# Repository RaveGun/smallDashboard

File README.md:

smallDashboard
==============

Small Dashboard

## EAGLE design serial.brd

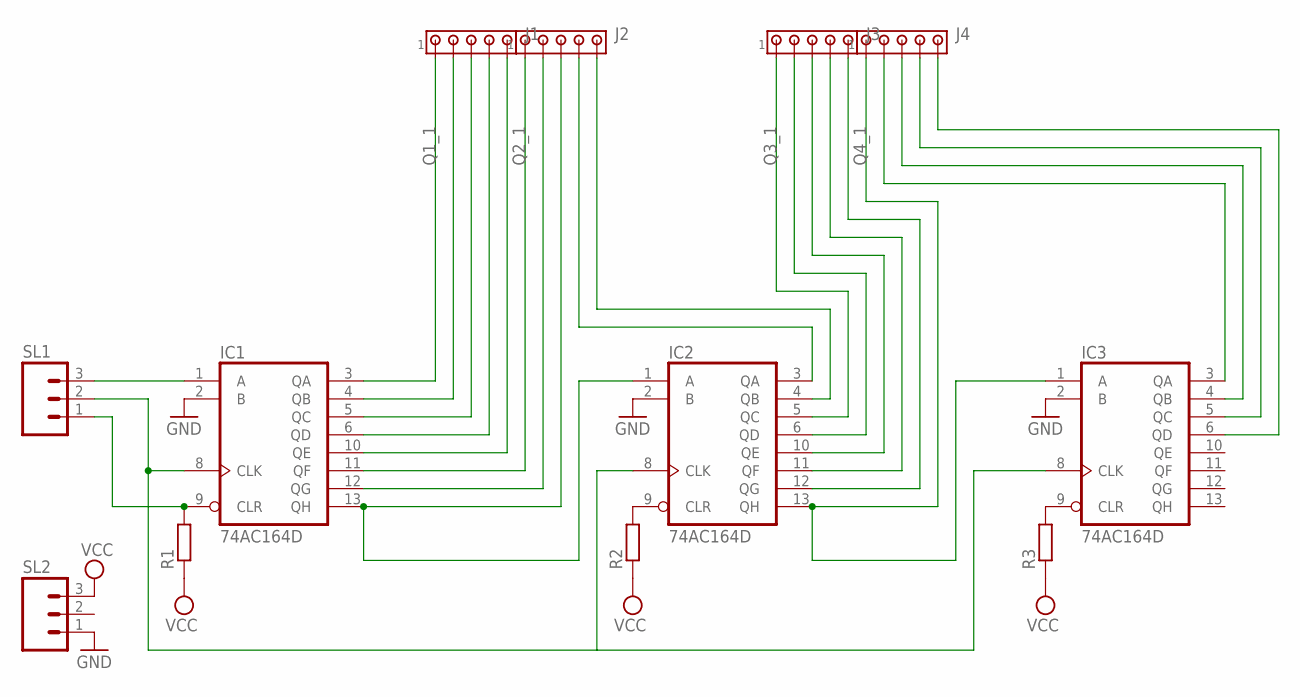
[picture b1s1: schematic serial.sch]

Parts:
IC1, IC2, IC3: 74AC164D; SO14
J1, J2, J3, J4: MTA05-100; 10X05MTA
R1, R2, R3: R-EU_R1206; R1206
SL1, SL2: M03; 03P

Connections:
GND: IC1.2 (B), IC1.7 (GND), IC2.2 (B), IC2.7 (GND), IC3.2 (B), IC3.7 (GND), SL2.1
unnamed: IC1.1 (A), SL1.3
unnamed: IC1.4 (QB), J1.2
unnamed: IC1.5 (QC), J1.3
unnamed: IC1.6 (QD), J1.4
unnamed: IC1.10 (QE), J1.5
unnamed: IC1.12 (QG), J2.2
unnamed: IC1.13 (QH), IC2.1 (A), J2.3
unnamed: IC1.8 (CLK), IC2.8 (CLK), IC3.8 (CLK), SL1.2
unnamed: IC1.9 (CLR), R1.2, SL1.1
unnamed: IC2.3 (QA), J2.4
unnamed: IC2.4 (QB), J2.5
unnamed: IC2.6 (QD), J3.2
unnamed: IC2.10 (QE), J3.3
unnamed: IC2.11 (QF), J3.4
unnamed: IC2.12 (QG), J3.5
unnamed: IC2.9 (CLR), R2.2
unnamed: IC3.3 (QA), J4.2
unnamed: IC3.4 (QB), J4.3
unnamed: IC3.5 (QC), J4.4
unnamed: IC3.6 (QD), J4.5
unnamed: IC3.9 (CLR), R3.2
Q1_1: IC1.3 (QA), J1.1
Q2_1: IC1.11 (QF), J2.1
Q3_1: IC2.5 (QC), J3.1
Q4_1: IC2.13 (QH), IC3.1 (A), J4.1
VCC: IC1.14 (VCC), IC2.14 (VCC), IC3.14 (VCC), R1.1, R2.1, R3.1, SL2.3

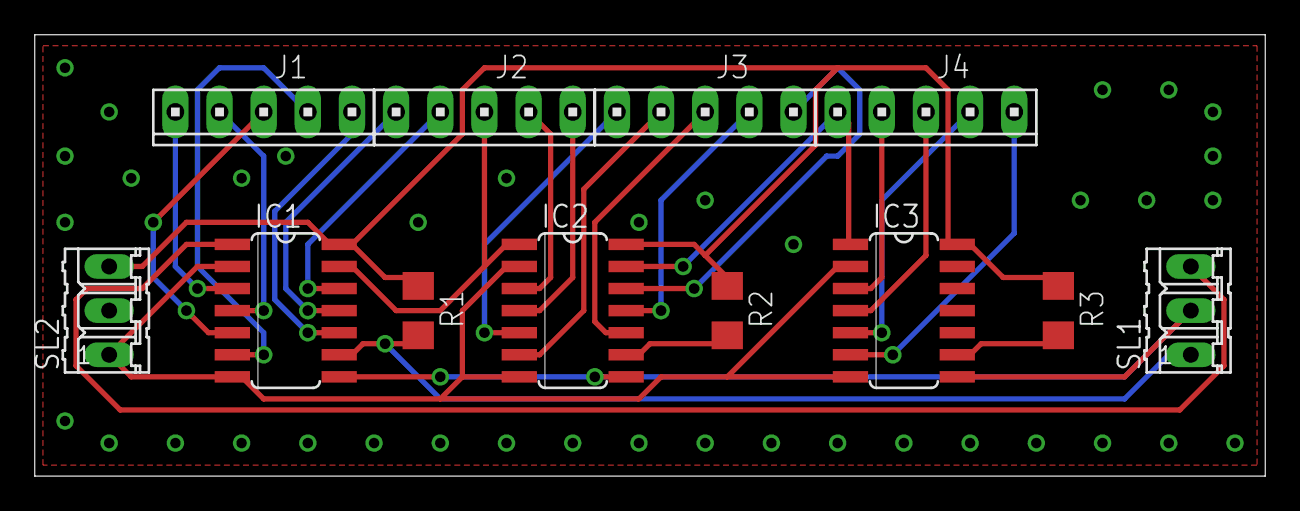
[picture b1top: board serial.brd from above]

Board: 2 copper layers, 70.8 x 25.4 mm, 12 parts (0 on the bottom side), 27 nets.

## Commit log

2013-04-20 Test update. Not worth mentioning.
